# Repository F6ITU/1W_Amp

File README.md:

# 1W_Amp
1W /20 dB RF linear amp

Attention : cet ampli est tiré du schéma du SDR Flex 1000. Ce n'est ni une oeuvre originale, 
ni un schéma open source. Seul le design  et l'implantation le sont. Toute diffusion commerciale est
donc strictement interdite sans l'accord de ses auteurs originels.

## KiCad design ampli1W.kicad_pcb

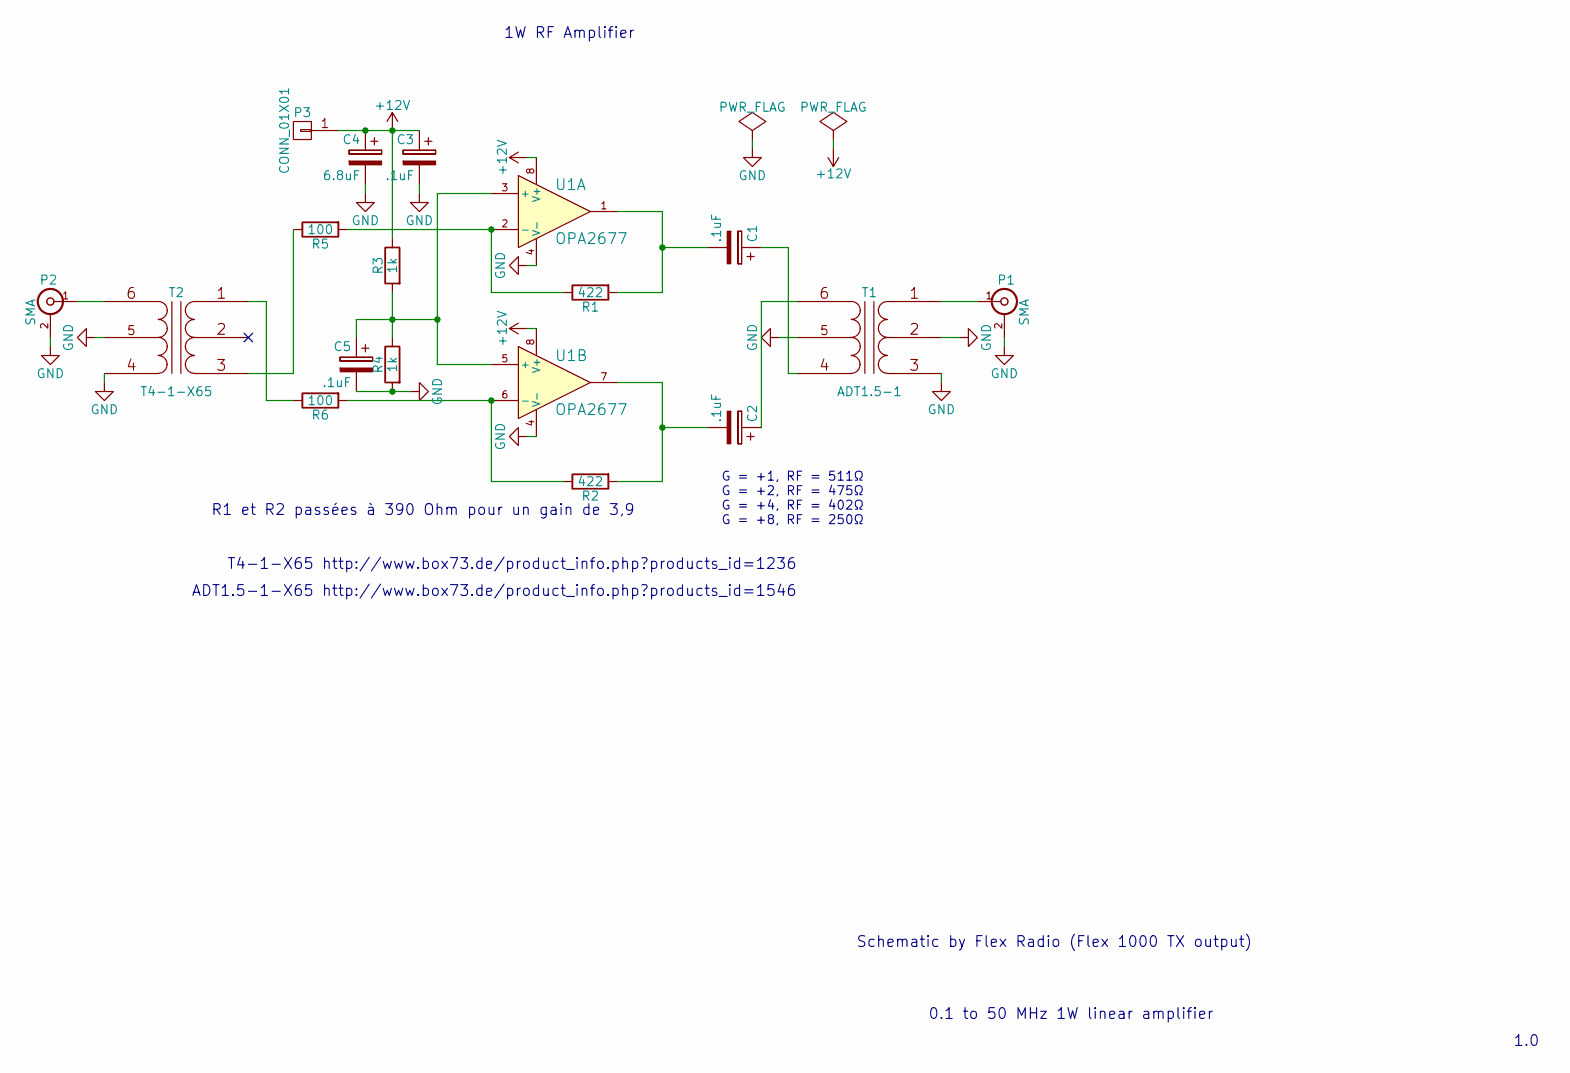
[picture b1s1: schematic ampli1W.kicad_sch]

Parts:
C1, C2, C3, C5: .1uF; R_1206_HandSoldering
C4: 6.8uF; c_tant_D
P1, P2: SMA; sma_smd_73251-135x
P3: CONN_01X01; PINTST
R1, R2: 422; C_0805_HandSoldering
R3, R4: 1k; C_0805_HandSoldering
R5, R6: 100; C_0805_HandSoldering
T1: ADT1.5-1; mdip_6
T2: T4-1-X65; mdip_6
U1: OPA2677; so-8

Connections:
+12V: C3.1, C4.1, P3.1, R3.1, U1.8 (V+)
GND: C3.2, C4.2, C5.2, P1.2 (Ext), P2.2 (Ext), R4.2, T1.2 (PM), T1.3 (PR2), T1.5 (S5), T2.4 (S1), T2.5 (S5), U1.4 (V-)
unnamed: C1.1, T1.4 (S1)
unnamed: C1.2, R1.2, U1.1
unnamed: C2.1, T1.6 (S2)
unnamed: C2.2, R2.2, U1.7
unnamed: C5.1, R3.2, R4.1, U1.3 (+), U1.5 (+)
unnamed: P1.1 (In), T1.1 (PR1)
unnamed: P2.1 (In), T2.6 (S2)
unnamed: R1.1, R5.2, U1.2 (-)
unnamed: R2.1, R6.2, U1.6 (-)
unnamed: R5.1, T2.3 (PR2)
unnamed: R6.1, T2.1 (PR1)

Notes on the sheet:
1W RF Amplifier
Schematic by Flex Radio (Flex 1000 TX output)
G = +1, RF = 511Ω G = +2, RF = 475Ω G = +4, RF = 402Ω G = +8, RF = 250Ω
ADT1.5-1-X65 http://www.box73.de/product_info.php?products_id=1546
1.0
0.1 to 50 MHz 1W linear amplifier
R1 et R2 passées à 390 Ohm pour un gain de 3,9
T4-1-X65 http://www.box73.de/product_info.php?products_id=1236

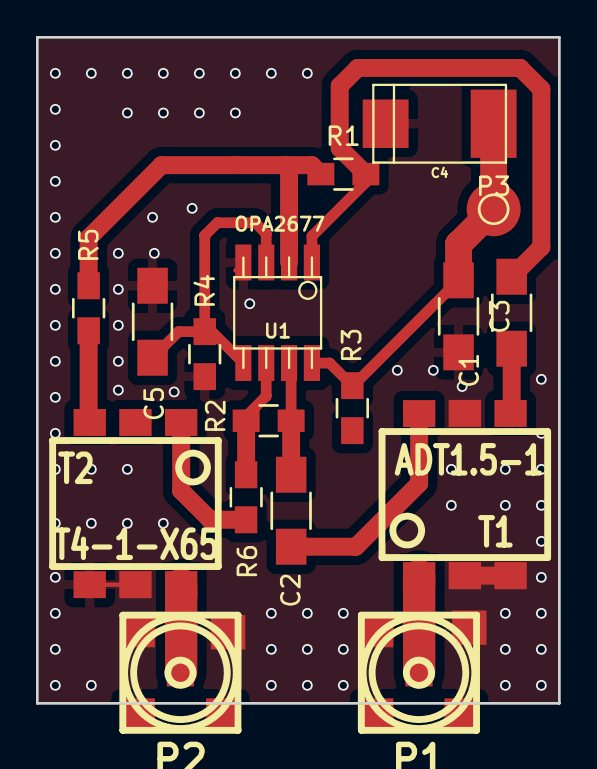
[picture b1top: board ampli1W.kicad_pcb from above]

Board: 2 copper layers, 29.0 x 37.0 mm, 17 parts (0 on the bottom side), 13 nets.

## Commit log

2016-05-19 version finale et stable
2016-05-19 modification du readme
2017-02-01 ajout image de l'ampli monté
2024-10-30 opened and saved with Kicad 8.0.4
